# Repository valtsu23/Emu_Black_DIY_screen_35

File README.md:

# Emu_Black_DIY_screen_35
Microcontroller reading sensor values from can bus and sending them to LCD screen. Also equipped with shift light and light sensor to control screen and shift light brightness. Also supports errorflags. It shows amount of errors and name of the first two errors. 

### Parts used (total about 130€):
- Adafruit Feather M4 CAN Express with ATSAME51
- Adafruit DS3231 Precision RTC Breakout (blue one)
- NeoPixel Stick - 8 x 5050 RGB LED
- MPM3610 5V 1.2A Buck Converter Breakout
- Nextion Discovery 3.5" (NX4832F035)
- CR1220 battery
- pcb own desing (from JLCPCB)
- JST-SM 4pin connector pair
- JST-XH female connector
- 2A fast diode
- tantalum capacitor 0,47µF 35V
- 1kohm 0,6W resistor
- photoresistor 200R - 500K
- side actuated tactile switch (TE 1-1825027-1)
- 1row 90 degree pin header 2,54mm
- 2 pin DuPont style housing
- 3 pin DuPont style housing
- 0,22mm2 stranded wire (24 AWG)
- 4x M3x5 button head screws
- 4x M3x10 countersunk screws
- 2x M3x8 countersunk screws
- magnetic car phone holder
- micro SD-card for uploading file to Nextion
- case printed from PETG with Creality Ender 3 V2

### Assembly:
One modification is needed for the Feather: Remove resistor next to the EN-pin (R8 on schematic). This disables the battery charger chip and then you can use the BAT-pin for 5v input. With this modification done you can connect it to computer with auxiliar power supply without worries. 
I had to drill bigger mounting holes to the Nextion to rotate the screen slightly, because screen wasn't installed straight to the pcb. Hot glue is used to the photoresistor. 

### Setup
Check Adafruit guide for setting up the Feather. Upload HMI file to sd card and Nextion will upload it when powered, then remove sd card. 
You also need to change the  baudrate to 115200 with code.py. Shift light setup guide is in the code.py. 

### Video of the shift light action
https://youtu.be/XviCfcwE8Wc

### Conclusion
The screen brightness is ok, but still could be brighter. Using black and white colours does help in the sunlight. 
Otherwise it has been working well. Early days still. 

### Pictures

Pcb on this picture is earlier prototype. Feather had a faulty voltage booster so I had to delete it. 

New one:

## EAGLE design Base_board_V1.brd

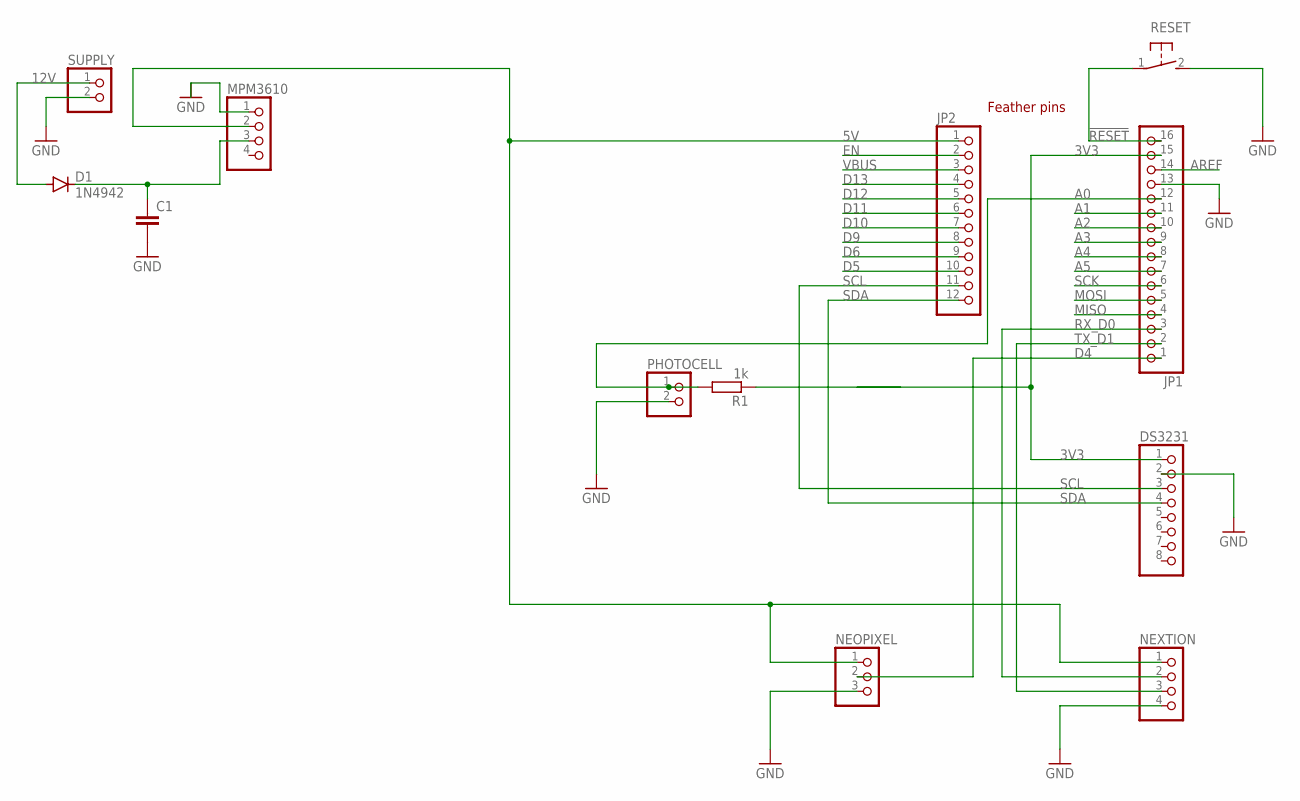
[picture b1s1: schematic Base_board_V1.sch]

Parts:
C1: C2,5-3; C2.5-3
D1: 1N4942; DO41-10
DS3231: HEADER-1X870MIL; 1X08_ROUND_70
JP1: HEADER-1X16ROUND; 1X16_ROUND
JP2: HEADER-1X12; 1X12_ROUND
MPM3610: PINHD-1X4; 1X04
NEOPIXEL: PINHD-1X3/90; 1X03/90
NEXTION: PINHD-1X4; 1X04
PHOTOCELL: PINHD-1X2/90; 1X02/90
R1: 1k; 0207/10
RESET: 31-XX; B3F-31XX
SUPPLY: PINHD-1X2; 1X02

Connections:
3V3: DS3231.1, JP1.15, R1.1
5V: JP2.1, MPM3610.2, NEOPIXEL.1, NEXTION.1
12V: D1.A, SUPPLY.1
!RESET: JP1.16, RESET.1
A0: JP1.12, PHOTOCELL.1, R1.2
A1: JP1.11
A2: JP1.10
A3: JP1.9
A4: JP1.8
A5: JP1.7
AREF: JP1.14
D4: JP1.1, NEOPIXEL.2
D5: JP2.10
D6: JP2.9
D9: JP2.8
D10: JP2.7
D11: JP2.6
D12: JP2.5
D13: JP2.4
EN: JP2.2
GND: C1.2, DS3231.2, JP1.13, MPM3610.1, NEOPIXEL.3, NEXTION.4, PHOTOCELL.2, RESET.2 (S), SUPPLY.2
MISO: JP1.4
MOSI: JP1.5
unnamed: C1.1, D1.C, MPM3610.3
RX_D0: JP1.3, NEXTION.2
SCK: JP1.6
SCL: DS3231.3, JP2.11
SDA: DS3231.4, JP2.12
TX_D1: JP1.2, NEXTION.3
VBUS: JP2.3

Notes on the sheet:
Feather pins

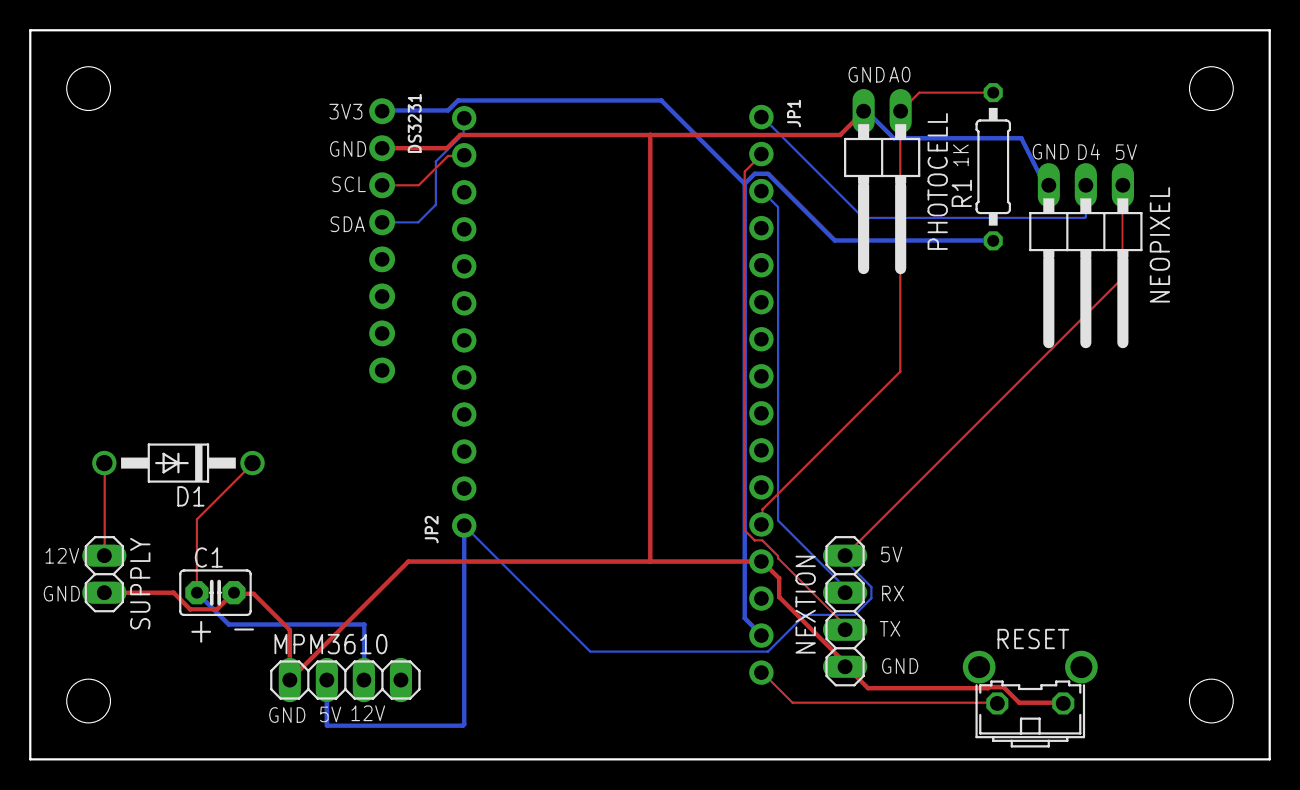
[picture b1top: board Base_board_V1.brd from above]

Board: 2 copper layers, 85.0 x 50.0 mm, 12 parts (0 on the bottom side), 12 nets.

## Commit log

2022-07-27 Create test
2022-07-27 Create erfes
2022-08-05 Update shift_light.py
    Fixed rpm going down bugs
2022-10-04 Update code.py
    # Version 2
    # Dimmer improved by slower reaction to ambient light change.
2022-10-18 Update code.py
    Exception Handling on I2C communication setup to prevent errors

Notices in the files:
parts and their libraries:
microbuilder: This work is placed in the public domain, and may be freely used for commercial and non-commercial work with the following conditions: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
